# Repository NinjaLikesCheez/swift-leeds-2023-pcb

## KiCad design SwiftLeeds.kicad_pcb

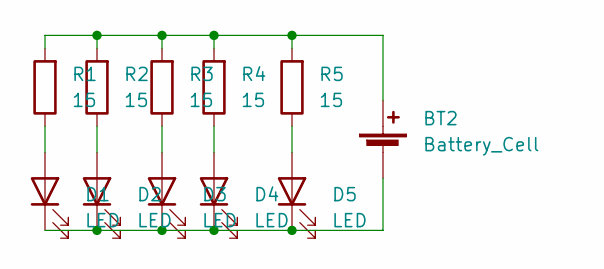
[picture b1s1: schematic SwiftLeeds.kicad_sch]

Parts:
BT2: Battery_Cell; BatteryHolder_Keystone_3034_1x20mm; LCSC C964834
D1, D2, D3, D4, D5: LED; LED_0805_Side; LCSC C693903
R1, R2, R3, R4, R5: 15; R_0805_2012Metric; LCSC C136900

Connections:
unnamed: BT2.1 (+), R1.2, R2.2, R3.2, R4.2, R5.2
unnamed: BT2.2 (-), D1.1 (K), D2.1 (K), D3.1 (K), D4.1 (K), D5.1 (K)
unnamed: D1.2 (A), R1.1
unnamed: D2.2 (A), R2.1
unnamed: D3.2 (A), R3.1
unnamed: D4.2 (A), R4.1
unnamed: D5.2 (A), R5.1

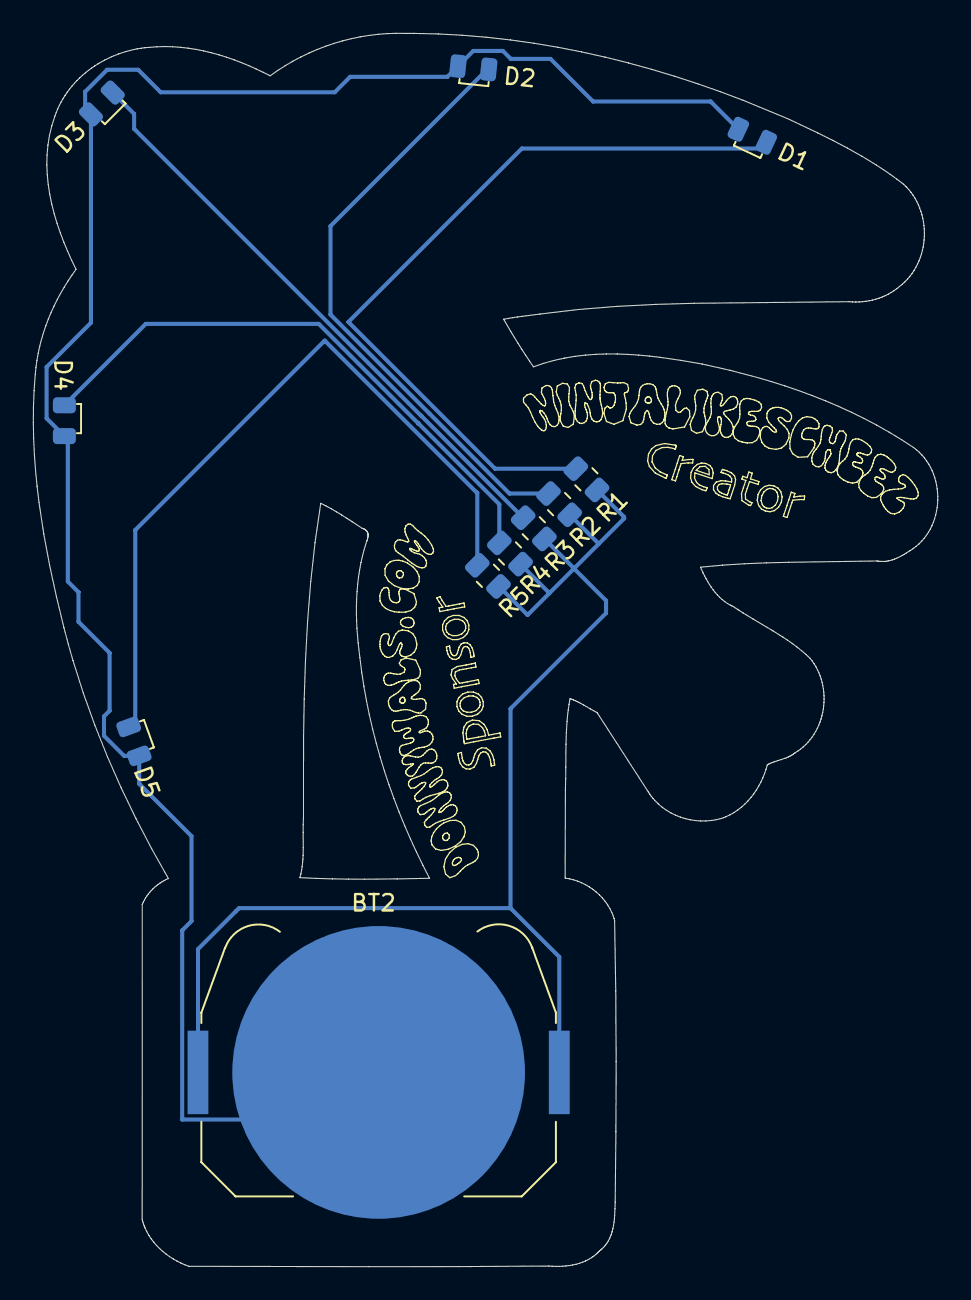
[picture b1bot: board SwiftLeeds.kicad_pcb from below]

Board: 2 copper layers, 55.0 x 75.0 mm, 11 parts (11 on the bottom side), 7 nets.

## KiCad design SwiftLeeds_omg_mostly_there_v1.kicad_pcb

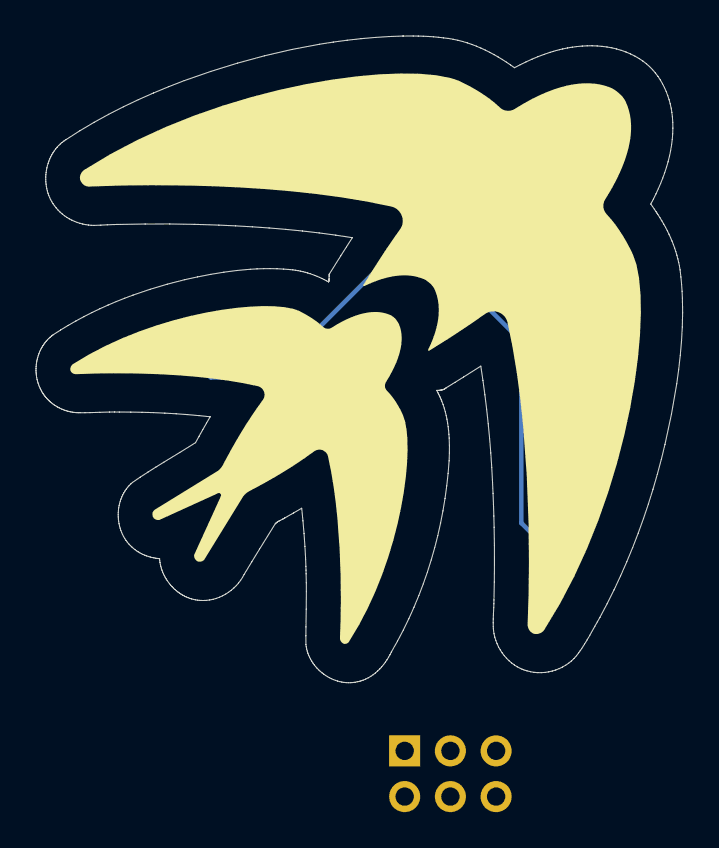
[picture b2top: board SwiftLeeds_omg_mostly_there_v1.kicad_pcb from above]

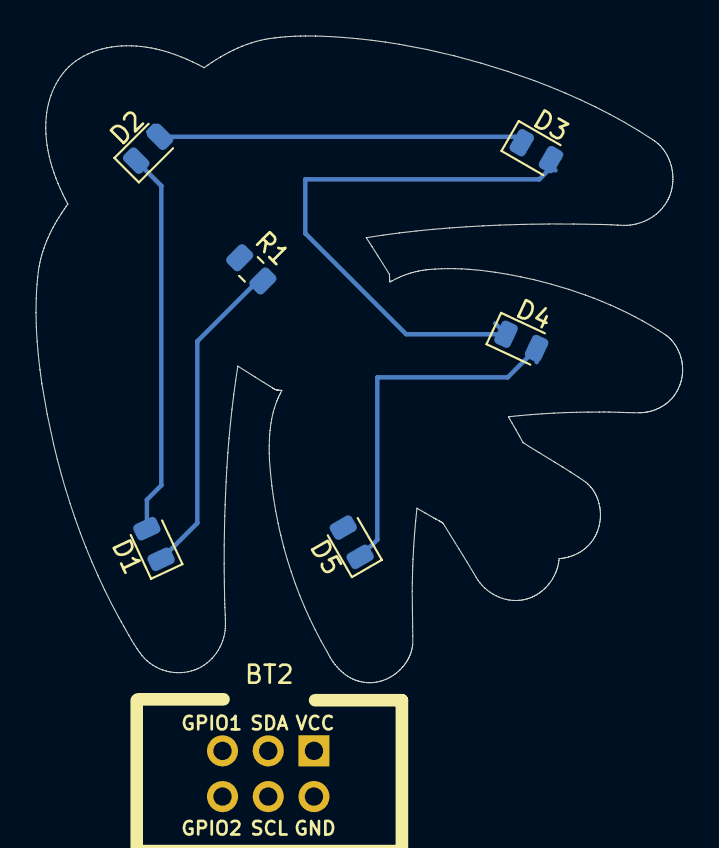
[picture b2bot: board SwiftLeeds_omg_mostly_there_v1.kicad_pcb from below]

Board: 2 copper layers, 35.9 x 35.9 mm, 7 parts (6 on the bottom side), 7 nets.

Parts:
BT2: Battery_Cell; Simple_Addon_v2-SAO-2x3
D1, D2, D3, D4, D5: LED; LED_0805_2012Metric
R1: R; R_0805_2012Metric

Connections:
unnamed: BT2.1 (+), D5.2 (A)
unnamed: BT2.2 (-), R1.1
unnamed: D1.1 (K), R1.2
unnamed: D1.2 (A), D2.1 (K)
unnamed: D2.2 (A), D3.1 (K)
unnamed: D3.2 (A), D4.1 (K)
unnamed: D4.2 (A), D5.1 (K)

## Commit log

2023-09-19 V.... 5 I think? Idk anymore, time has become one long unending torture
2023-09-19 lol just fucking joking - one more tweak _as I went to order_ goddamn it
2023-09-19 lmao, what the fuck is wrong with me - version 7 lets goooo
2023-09-19 Okay, one more tweak because of some supply issues with the battery case
2023-10-07 clean up - place is a fucking tip
